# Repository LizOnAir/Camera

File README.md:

# Camera

This camera consist of a custom PCB and buttons as well as a 2.4 inch tft display with sd card slot, that can capture picture. I made this project to improve my knowledge about PCB design and also I personally really wanna make a retro camera with noisy resolution. Through this project, I learnt about high speed signals, parallel signals and heat management.

## Features:
- auto-focus 
- power with battery
- capture photos
- view photos

## CAD Model:

Made in Fusion360.Liz
Access files in [CAD folder](https://github.com/LizOnAir/Camera/tree/main/CAD).

## Assembly
Steps:
1.  Insert 4 heatset onto the 4 mounting holes in the bottom case.
2.  Insert the PCB into the bottom case.
3.  Using hot glue, stick the buttons onto the tactile switches.
4.  Align the holes of PCB onto the holes of the bottom case.
5.  Cover the top case over the bottom case.
6.  Screw them tight together.
7.  Charge the battery and use!!

## PCB
Here's my PCB! It was made in KiCad. 
### Schematic
Main board

Camera - OV5640

### PCB

Access files in [PCB folder](https://github.com/LizOnAir/Camera/tree/main/PCB).

## Firmware
I use Arduino IDE to program this camera
- dual state
    - capture image
    - review image

Access files in [Firmware folder](https://github.com/LizOnAir/Camera/tree/main/Firmware).

## BOM:
Here should be [everything](https://docs.google.com/spreadsheets/d/14nMMweMc_XzQDbo61nnmqZUTtTscH9UbB8BGQstIzH4/edit?usp=sharing) you need to make this:
- 1x PCBA
- 1x Ov5640
- 1x 3.7V Lipo Battery 500mAh
- 3x Tactile buttons
- 1x Slide switch
- 1x PH connector
- 1x Micro SD card
- 2.4 inch tft display
- 4x M3 14mm Screws
- 4x M3 OD4.2 L 4 Heatset inserts
- 1x 3d printed case

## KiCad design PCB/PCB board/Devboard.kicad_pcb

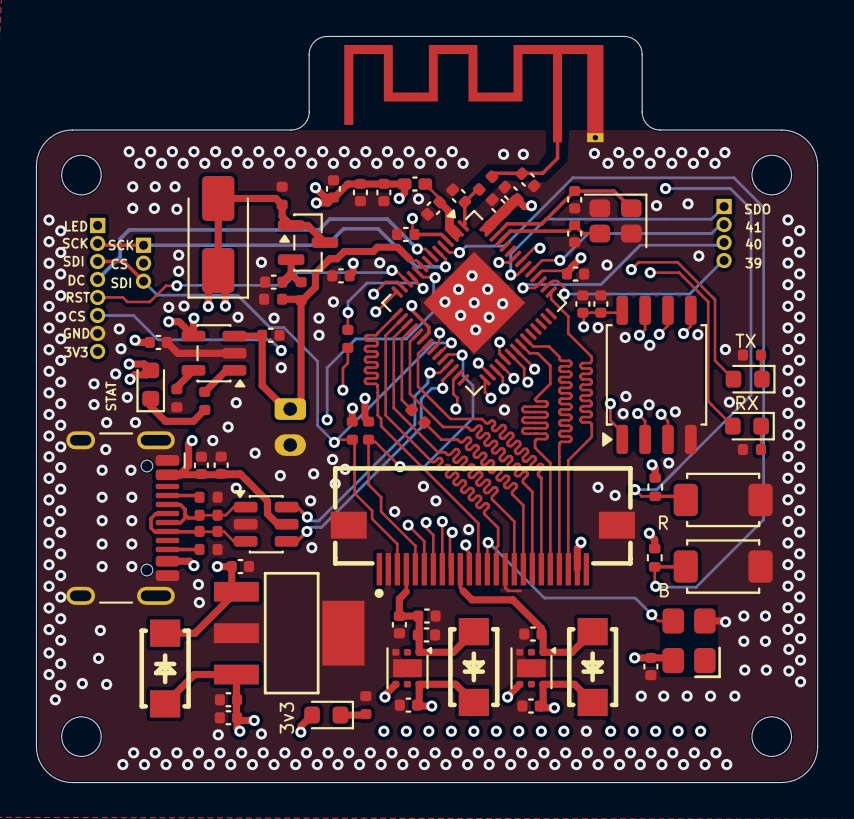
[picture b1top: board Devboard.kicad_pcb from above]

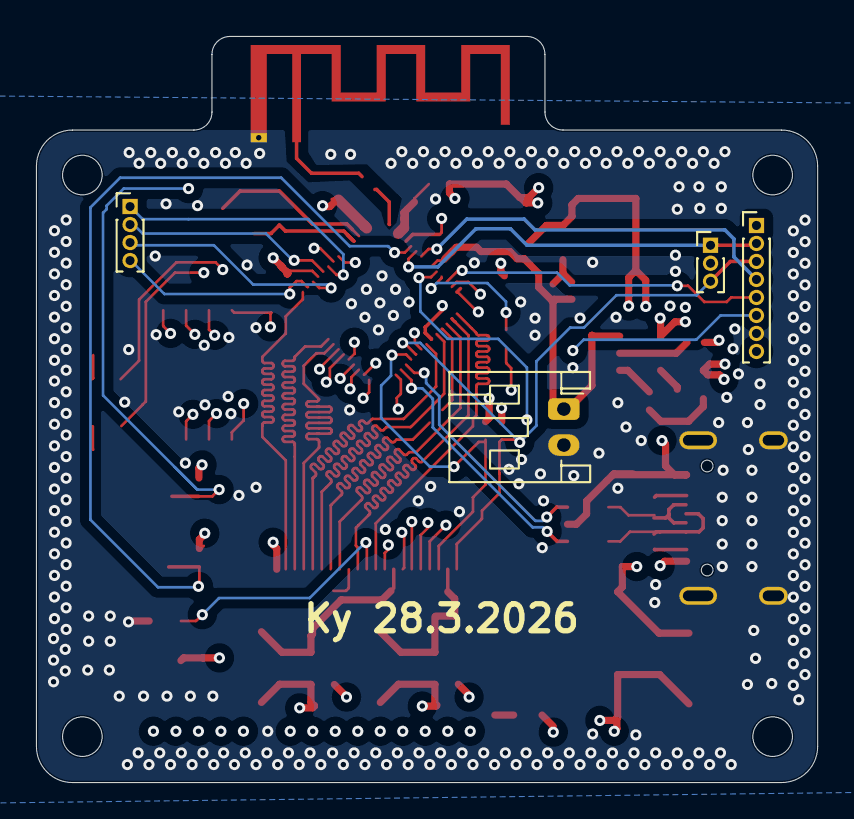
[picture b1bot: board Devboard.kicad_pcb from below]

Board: 4 copper layers, 43.4 x 41.5 mm, 77 parts (4 on the bottom side), 62 nets.

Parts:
AE1: Antenna_Chip; Texas_SWRA117D_2.4GHz_Left
C1, C2, C8, C12, C13, C14, C17, C20, C33, C34: 0.1uF; C_0402_1005Metric
C3, C7, C18, C21, C27, C28, C30: 1uF; C_0402_1005Metric
C4, C5, C10, C11, C26: 10UF; C_0402_1005Metric
C6, C19: 10nF; C_0402_1005Metric
C9, C15: 3pF; C_0402_1005Metric
C22, C23: 22pF; C_0402_1005Metric
C31, C32: 4.7UF; C_0402_1005Metric
CN1: FPC-SMD_KH-FG0.5-H2.0-24PIN
CN2: PH-2AK; JST_PH_S2B-PH-K_1x02_P2.00mm_Horizontal
D1, D3, D4, D6: LED; LED_0603_1608Metric
D2: SS14; D_SMA
D5, D7, D8: SS14
Flash1: Flash; SW_TS-1088-AR02016
J1: USB_C_Receptacle_USB2.0_14P; USB_C_Receptacle_HCTL_HC-TYPE-C-16P-01A
J3: Conn_01x08_Pin; PinHeader_1x08_P1.00mm_Vertical
J4: Conn_01x03_Pin; PinHeader_1x03_P1.00mm_Vertical
J5: Conn_01x04_Pin; PinHeader_1x04_P1.00mm_Vertical
L1: 2nH; L_0402_1005Metric_Pad0.77x0.64mm_HandSolder
L2: 2.4nH; L_0402
Q1: AO3401A; SOT-23
R1, R2: 5.1k; R_0402
R3, R10, R21, R22: 1k; R_0402
R4, R6: 10k; R_0402_1005Metric
R5, R11: 0; R_0402
R7, R8, R9: 470; R_0402
R14, R15: 33; R_0402
R18: 100k; R_0402
R19, R20: 200k; R_0402
Reset1: Reset; SW_TS-1088-AR02016
U1: c; QFN-56-1EP_7x7mm_P0.4mm_EP4x4mm
U3: MCP73831T-2DCI/OT; SOT-23-5
U4: W25Q128JVS; SOIC-8_5.3x5.3mm_P1.27mm
U5: TLV75515PDRV; WSON-6-1EP_2x2mm_P0.65mm_EP1x1.6mm
U6: TLV75518PDRV; WSON-6-1EP_2x2mm_P0.65mm_EP1x1.6mm
U7: USBLC6-2SC6; SOT-23-6
U8: AP2114HA-3_3TRG1
X2: 3N24000G33YC; OSC-SMD_4P-L3.2-W2.5-BL
Y1: 40MHz(10ppm); Crystal_SMD_2520-4Pin_2.5x2.0mm

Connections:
DAT0: CN1.19 (Y2), U1.21 (XTAL_32K_P)
DAT1: CN1.21 (Y3), U1.37 (SPICLK_P)
DAT2: CN1.22 (Y4/MDN0), U1.43 (GPIO38)
DAT3: CN1.20 (Y5/MDP0), U1.36 (SPICLK_N)
DAT4: CN1.18 (Y6/MCN), U1.19 (GPIO14)
DAT5: CN1.16 (Y7/MCP), U1.17 (GPIO12)
DAT6: CN1.14 (Y8/MDN1), U1.16 (GPIO11)
DAT7: CN1.12 (Y9/MDP1), U1.15 (GPIO10)
GND: AE1.2 (PCB_Trace), C1.2, C2.2, C3.2, C4.2, C5.2, C6.2, C7.2, C8.2, C9.2, C10.2, C11.2, C12.2, C13.2, C14.2, C15.2, C17.2, C18.2, C19.2, C20.2, C21.2, C22.2, C23.2, C26.2, C27.2, C28.2, C30.2, C31.2, C32.2, C33.2, C34.2, CN1.2 (AGND), CN1.15 (DGND), CN1.25 (GND), CN1.26 (GND), CN2.2, Flash1.1, J1.A1 (GND), J1.A12 (GND), J1.B1 (GND), J1.B12 (GND), J1.S1 (SHIELD), J3.7, R1.2, R2.2, R3.2, R7.1, R8.1, R9.1, R18.1, R20.2, Reset1.2, U1.57 (GND), U3.2 (V_{SS}), U4.4 (GND), U5.3 (GND), U5.7 (GND), U6.3 (GND), U6.7 (GND), U7.2 (GND), U8.2 (GND), U8.4 (GND), X2.2 (GND), Y1.2 (G), Y1.4 (G)
IO0: Flash1.2, R6.1, U1.5 (GPIO0)
IO1: J3.2, J4.1, U1.6 (GPIO1)
IO2: J3.4, U1.7 (GPIO2)
IO4/BAT: C11.1, CN2.1, R19.2, R20.1, U1.9 (GPIO4), U3.3 (V_{BAT})
IO7: J3.5, U1.12 (GPIO7)
IO13/PCLK: R11.1, U1.18 (GPIO13)
IO21: J3.6, U1.27 (GPIO21)
IO38/VSYNC: R5.1, U1.11 (GPIO6)
IO39: J5.4, U1.44 (MTCK)
IO40: J5.3, U1.45 (MTDO)
IO41: J5.2, U1.47 (MTDI)
IO42: J5.1, U1.48 (MTMS)
IO47/HREF: CN1.9 (HREF), U1.13 (GPIO8)
unnamed: AE1.1 (FEED), C9.1, L2.2
unnamed: C1.1, L1.2, U1.2 (VDD3P3), U1.3 (VDD3P3)
unnamed: CN1.17 (PCLK), R11.2
unnamed: CN1.7 (VSYNC), R5.2
unnamed: D1.1 (K), R10.2
unnamed: D3.1 (K), R7.2
unnamed: D4.1 (K), R8.2
unnamed: D6.1 (K), R9.2
unnamed: J1.A5 (CC1), R1.1
unnamed: J1.B5 (CC2), R2.1
unnamed: J1.A6 (D+), J1.B6 (D+), R15.1, R15.2, U7.3 (I/O2)
unnamed: J1.A7 (D-), J1.B7 (D-), R14.1, R14.2, U7.1 (I/O1)
unnamed: C26.1, Q1.2 (S), R19.1
unnamed: C14.1, R4.2, Reset1.1, U1.4 (CHIP_PU)
unnamed: C15.1, L2.1, U1.1 (LNA_IN)
unnamed: C22.1, U1.53 (XTAL_N), Y1.3
unnamed: C23.1, U1.54 (XTAL_P), Y1.1
unnamed: R3.1, U3.5 (PROG)
unnamed: R10.1, U3.1 (STAT)
PWDN: CN1.8 (PWDN), U1.14 (GPIO9)
RESET: CN1.6 (RESET), U1.10 (GPIO5)
RX: D6.2 (A), U1.50 (U0RXD)
SCL: CN1.5 (SIO-C), R22.2, U1.24 (GPIO18)
SDA: CN1.3 (SIO-D), J3.3, J4.3, R21.2, U1.23 (GPIO17)
SPICLK: U1.33 (SPICLK), U4.6 (CLK)
SPICS0: U1.32 (SPICS0), U4.1 (~CS)
SPID: U1.35 (SPID), U4.5 (DI/IO_{0})
SPIHD: U1.30 (SPIHD), U4.7 (~HOLD/~RESET/IO_{3})
SPIQ: U1.34 (SPIQ), U4.2 (DO/IO_{1})
SPIWP: U1.31 (SPIWP), U4.3 (~WP/IO_{2})
TX: D4.2 (A), U1.49 (U0TXD)
USB_D+: U1.26 (GPIO20/USB_D+), U7.4 (I/O2)
USB_D-: U1.25 (GPIO19/USB_D-), U7.6 (I/O1)
VDDIO: C2.1, C3.1, C4.1, C6.1, C7.1, C12.1, C13.1, C17.1, C18.1, C19.1, C27.1, C31.1, CN1.11 (DOVDD), CN1.23 (AF-VDD), D3.2 (A), D5.2 (A), D7.1 (K), D8.1 (K), J3.1, J3.8, L1.1, R4.1, R6.2, R21.1, R22.1, U1.20 (VDD3P3_RTC), U1.46 (VDD3P3_CPU), U1.55 (VDDA), U1.56 (VDDA), U5.4 (EN), U5.6 (IN), U6.4 (EN), U6.6 (IN), U8.3 (OUT), X2.4 (VDD)
VDD_1.5V: C28.1, CN1.10 (DVDD), D7.2 (A), U5.1 (OUT)
VDD_2.8V: C30.1, C33.1, C34.1, CN1.4 (AVDD), D8.2 (A), U6.1 (OUT)
VDD_SPI: C20.1, C21.1, U1.29 (VDD_SPI), U4.8 (VCC)
VSYS: C5.1, C8.1, C10.1, C32.1, D1.2 (A), D2.1 (K), D2.2 (A), D5.1 (K), J1.A4 (VBUS), J1.A9 (VBUS), J1.B4 (VBUS), J1.B9 (VBUS), Q1.1 (G), Q1.3 (D), R18.2, U3.4 (V_{DD}), U7.5 (VBUS), U8.1 (IN)
XCLK: CN1.13 (XCLK), X2.3 (OUT)
XTAL_32P: J4.2, U1.22 (XTAL_32K_N)

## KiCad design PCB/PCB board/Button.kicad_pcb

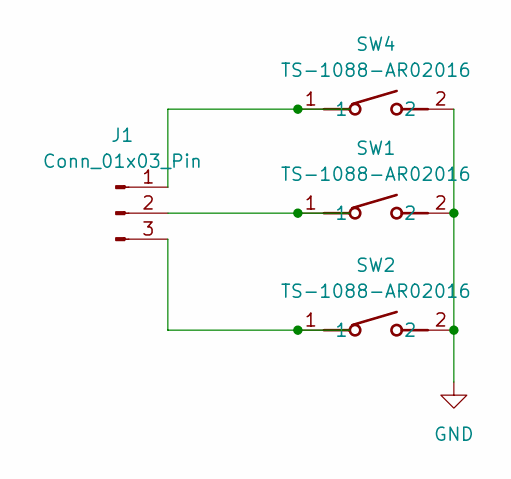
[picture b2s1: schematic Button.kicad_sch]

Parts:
J1: Conn_01x03_Pin; PinHeader_1x03_P1.00mm_Vertical
SW1, SW2, SW4: TS-1088-AR02016; C13828; Manufacturer Part TS-1088-AR02016; LCSC C720477

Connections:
GND: SW1.2, SW2.2, SW4.2
unnamed: J1.1, SW4.1
unnamed: J1.2, SW1.1
unnamed: J1.3, SW2.1

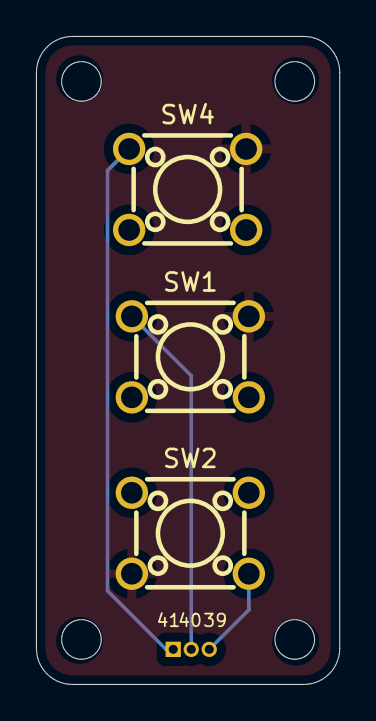
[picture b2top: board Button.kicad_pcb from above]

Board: 2 copper layers, 16.8 x 36.0 mm, 4 parts (1 on the bottom side), 4 nets.

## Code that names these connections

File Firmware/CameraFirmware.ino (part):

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 *
 * ─── 引脚分配 ────────────────────────────────────────────────────────────────
 *  Camera (DVP 并行):
 *    PWDN=9  RESET=5  XCLK=内部  SIOD=17  SIOC=18
 *    Y2-Y9 = 16,47,30,48,14,12,11,10
 *    VSYNC=6  HREF=8  PCLK=13
 *
 *  TFT ST7735 (SPI):
 *    MOSI=2   SCLK=1   CS=21   DC=7   RST=3
 *    ※ MOSI 已从 GPIO17 改为 GPIO2，与摄像头 SCCB 完全隔离，无冲突
 *
 *  SD Card (SD_MMC 1-bit):
 *    由 SD_MMC 库管理，1-bit 模式
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  if (totalPictures < 0 || totalPictures > 9999) totalPictures = 0;
  Serial.printf("[EEPROM] Total pictures stored: %d\n", totalPictures);

  // ── Step 1: 显示器初始化（GPIO2=MOSI 与摄像头无冲突，先启动）────────────
  if (!initDisplay()) {
    Serial.println("[ERROR] Display init failed!");
    // 不 halt，继续运行
  }

  // ── Step 2: 摄像头初始化（GPIO17=SCCB SDA，与 TFT 引脚完全隔离）─────────
  if (!initCamera()) {
    tft.fillScreen(TFT_RED);
    tft.setTextColor(TFT_WHITE, TFT_RED);
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  config.pin_d5       = Y7_GPIO_NUM;
  config.pin_d6       = Y8_GPIO_NUM;
  config.pin_d7       = Y9_GPIO_NUM;
  config.pin_xclk     = XCLK_GPIO_NUM;
  config.pin_pclk     = PCLK_GPIO_NUM;
  config.pin_vsync    = VSYNC_GPIO_NUM;
  config.pin_href     = HREF_GPIO_NUM;
  config.pin_sccb_sda = SIOD_GPIO_NUM;
  config.pin_sccb_scl = SIOC_GPIO_NUM;
  config.pin_pwdn     = PWDN_GPIO_NUM;
  config.pin_reset    = RESET_GPIO_NUM;
  config.xclk_freq_hz = 20000000;
  config.pixel_format = PIXFORMAT_JPEG;
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
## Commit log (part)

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2026-04-10 Create e
2026-04-10 Add README for camera project with features and PCB info
    Added detailed information about the camera, including features, CAD model, PCB schematics, and BOM link.
2026-04-10 Rename Untitled.kicad_prl to Camera.kicad_prl
2026-04-10 Rename Untitled.kicad_pro to Camera.kicad_pro
2026-04-10 Add Camera schematic file
2026-04-10 Rename PCB/Button.kicad_sch to PCB/Schematic/Button.kicad_sch
2026-04-10 Rename PCB/Devboard.kicad_sch to PCB/Schematic/Devboard.kicad_sch
2026-04-10 Rename PCB/Button.kicad_pcb to PCB/PCB board/Button.kicad_pcb
2026-04-10 Rename PCB/Devboard.kicad_pcb to PCB/PCB board/Devboard.kicad_pcb
2026-04-10 Rename PCB/Button.kicad_prl to PCB/Achive/Button.kicad_prl
2026-04-10 Rename PCB/Button.kicad_pro to PCB/Achive/Button.kicad_pro
2026-04-10 Rename PCB/Camera.kicad_prl to PCB/Achive/Camera.kicad_prl
2026-04-10 Rename PCB/Devboard.kicad_pro to PCB/Achive/Devboard.kicad_pro
2026-04-10 Rename PCB/Devboard.kicad_prl to PCB/Achive/Devboard.kicad_prl
2026-04-10 Rename PCB/Camera.kicad_pro to PCB/Achive/Camera.kicad_pro
2026-04-10 Rename CameraFirmware.ino to Firmware/CameraFirmware.ino
2026-04-14 Rename Capture the moment.pdf to ZineCaptureTheMoment.pdf
2026-04-14 Rename Capture the moment.pdf to ZineCapture the moment.pdf
2026-04-14 Enhance README with project insights and links
    Expanded project description with additional learning insights and added links to PCB and Firmware folders.
2026-04-27 Rename PCB/Devboard.zip to PCB/Gerbers/Devboard.zip
